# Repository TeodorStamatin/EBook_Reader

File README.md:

# EBook_Reader

## Block Diagram

## BOM (Bill Of Materials)

| Component  | Supplier Link | Datasheet |
|------------|---------------|-----------|
| 112A-TAAR-R03 | [Model](https://www.snapeda.com/parts/112A-TAAR-R03/Attend/view-part/) | [Datasheet](https://www.snapeda.com/parts/112A-TAAR-R03/Attend/datasheet/) |
| 744043680 | [Model](https://ro.mouser.com/ProductDetail/Wurth-Elektronik/744043680?qs=PGXP4M47uW6VkZq%252BkzjrHA%3D%3D) | [Datasheet](https://www.we-online.com/components/products/datasheet/744043680.pdf) |
| BD5229G-TR | [Model](https://www.digikey.ee/en/models/658502) | [Datasheet](https://www.rohm.com/datasheet?p=BD5229G&dist=Digi-key&media=referral&source=digi-key.com&campaign=Digi-key) |
| Capacitor 0402 | [Model](https://componentsearchengine.com/part-view/CC0402MRX5R5BB106/YAGEO) | [Datasheet](https://componentsearchengine.com/Datasheets/2/CC0402MRX5R5BB106.pdf) |
| CPH3225A | [Model](https://www.snapeda.com/parts/CPH3225A/Seiko+Instruments/view-part/?ref=eda) | [Datasheet](https://www.snapeda.com/parts/CPH3225A/Seiko%20Instruments/datasheet/) |
| Custom Button | [Model](https://industry.panasonic.com/global/en/products/control/switch/light-touch/number/evqpuj02k) | [Datasheet](https://industry.panasonic.com/global/en/downloads?tab=catalog&small_g_cd=203&part_no=EVQPUJ02K) |
| DS3231SN | [Model](https://www.snapeda.com/parts/DS3231SN%23/Analog+Devices/view-part/?ref=eda) | [Datasheet](https://www.snapeda.com/parts/DS3231SN%23/Analog%20Devices/datasheet/) |
| ESP32 WROVER 0805 Capacitor | [Model](https://ro.mouser.com/ProductDetail/KYOCERA-AVX/SD0805S020S1R0?qs=jCA%252BPfw4LHbpkAoSnwrdjw%3D%3D) | [Datasheet](https://ro.mouser.com/datasheet/2/40/schottky-3165252.pdf) |
| ESP32 WROVER BME680 Sensor | [Model](https://www.digikey.ro/en/models/7401317) | [Datasheet](https://www.bosch-sensortec.com/media/boschsensortec/downloads/datasheets/bst-bme680-ds001.pdf) |
| ESP32 WROVER MCP73831 Power Management | [Model](https://www.snapeda.com/parts/MCP73831T-2ACI/OT/Microchip/view-part/) | [Datasheet](https://www.snapeda.com/parts/MCP73831T-2ACI/OT/Microchip/datasheet/) |
| ESP32C6 Varistor 1812 | [Model](https://www.snapeda.com/parts/RC0603JR-070RL/Yageo/view-part/) | [Datasheet](https://www.snapeda.com/parts/RC0603JR-070RL/Yageo/datasheet/) |
| ESP32C6 WROOM-1-N8 | [Model](https://www.snapeda.com/parts/ESP32-C6-WROOM-1-N8/Espressif+Systems/view-part/?ref=eda) | [Datasheet](https://www.snapeda.com/parts/ESP32-C6-WROOM-1-N8/Espressif%20Systems/datasheet/) |
| FH34SRJ-24S-0.5SH | [Model](https://www.snapeda.com/parts/FH34SRJ-24S-0.5SH(99)/Hirose/view-part/) | [Datasheet](https://www.snapeda.com/parts/FH34SRJ-24S-0.5SH(99)/Hirose%20Connector/datasheet/) |
| LED Chip 0603 | [Model](https://grabcad.com/library/0603-smd-led-1) | [Datasheet](https://www.snapeda.com/parts/KP-1608SURCK/Kingbright/datasheet/) |
| MAX17048G+T10 | [Model](https://www.snapeda.com/parts/MAX17048G+T10/Analog+Devices/view-part/?ref=eda) | [Datasheet](https://www.snapeda.com/parts/MAX17048G+T10/Analog%20Devices/datasheet/) |
| MBR0530 Schottky Diode | [Model](https://www.snapeda.com/parts/MBR0530/Onsemi/view-part/?ref=eda) | [Datasheet](https://www.snapeda.com/parts/MBR0530/ON%20Semiconductor/datasheet/) |
| PGB1010603MR | [Model](https://www.snapeda.com/parts/PGB1010603MR/Littelfuse/view-part/?ref=eda) | [Datasheet](https://www.snapeda.com/parts/PGB1010603MR/Littelfuse%20Inc./datasheet/) |
| QWIIC Connector | [Model](https://www.snapeda.com/parts/PRT-14417/SparkFun/view-part/) | [Datasheet](https://www.snapeda.com/parts/PRT-14417/SparkFun%20Electronics/datasheet/) |
| RCL CPOL 3528 | [Model](https://www.snapeda.com/parts/TAJB475K025RNJ/AVX/view-part/?ref=dk&t=capacitor%203528&con_ref=None) | [Datasheet](https://s3.amazonaws.com/snapeda/datasheet/TAJB475K025RNJ_AVX.pdf) |
| Resistor 0402 | [Model](https://componentsearchengine.com/part-view/R0402%201%25%20100%20K%20(RC0402FR-07100KL)/YAGEO) | [Datasheet](https://www.yageo.com/upload/media/product/products/datasheet/rchip/PYu-RC_Group_51_RoHS_L_12.pdf) |
| SI1308EDL-T1-GE3 MOSFET | [Model](https://www.snapeda.com/parts/SI1308EDL-T1-GE3/Vishay+Siliconix/view-part/?ref=eda) | [Datasheet](https://www.snapeda.com/parts/SI1308EDL-T1-GE3/Vishay%20Siliconix/datasheet/) |
| SJ | [Model](https://grabcad.com/library/solder-jumpers-1) | [Datasheet]() |
| TPTP20R | [Model](https://ro.mouser.com/ProductDetail/Adafruit/3825?qs=%252bEew9%252b0nqrAn6n76%252bB5vZg%3D%3D&utm_source=findchips&utm_medium=aggregator&utm_campaign=3825&utm_term=3825&utm_content=Adafruit&_gl=1*1t6jdbp*_ga*MTQ5NTQ1ODI1LjE3NDMyMzgzNTY.*_ga_15W4STQT4T*MTc0Mzc4MDU5Ni4xMi4xLjE3NDM3ODM2MzIuNDIuMC4w) | [Datasheet](https://cdn-shop.adafruit.com/product-files/3825/3825_diagram.PDF) |
| USB4110-GF-A | [Model](https://componentsearchengine.com/part-view/USB4110-GF-A/GCT%20(GLOBAL%20CONNECTOR%20TECHNOLOGY)) | [Datasheet](https://gct.co/files/drawings/usb4110.pdf) |
| USBLC6-2SC6Y | [Model](https://www.snapeda.com/parts/USBLC6-2SC6Y/STMicroelectronics/view-part/?ref=eda) | [Datasheet](https://www.snapeda.com/parts/USBLC6-2SC6Y/STMicroelectronics/datasheet/) |
| W25Q512JVEIQ | [Model](https://www.digikey.ro/en/models/10244706) | [Datasheet](https://www.winbond.com/resource-files/W25Q512JV%20SPI%20RevB%2006252019%20KMS.pdf) |
| XC6220A331MR-G | [Model](https://componentsearchengine.com/part-view/XC6220A331MR-G/Torex) | [Datasheet](https://product.torexsemi.com/system/files/series/xc6220.pdf) |

## Hardware Description
1. Microcontroller - ESP32-C6-WROOM-1-N8
The ESP32-C6 is the core processing unit responsible for handling all system operations, communication with sensors and modules, and power management.
- Architecture: RISC-V 32-bit
- Clock Speed: 160 MHz
- Wireless Connectivity: 2.4 GHz Wi-Fi 6, Bluetooth 5.0

2. Power Management & Battery
Battery Type: Li-Po (Lithium Polymer)
- Capacity: 3.7V, 1800mAh
- Charging Circuit: MCP73831T
- Input Voltage: 5V via USB-C
- Protection Features: Overcharge and deep discharge protection
- Voltage Regulator: LDO regulator ensures a stable 3.3V power supply to all components.

3. Display - E-Paper (E-Ink) Screen
- Size: 7.5 inches
- Resolution: 800x480 pixels
- Communication Interface: SPI

4. SD Card Module
- Type: MicroSD (Supports FAT32)
- Interface: SPI

5. External NOR Flash
- Capacity: 64MB
- Interface: SPI

6. Environmental Sensor - BME688
- Functions: Measures temperature, humidity, air pressure, and gas levels.
- Communication Interface: I2C

7. Real-Time Clock (RTC) - DS3231SN
- Functionality: Maintains time and date even when the system is powered off.
- Communication Interface: I2C

8. USB-C Connector & ESD Protection
- Functionality: Provides power input and data transfer capability.
- Protection: Integrated ESD protection and Schottky diode for reverse polarity safety.

9. Buttons & User Input
- Tactile Push Buttons

10. Communication Interfaces
- GPIO: Used for button controls and general I/O operations.
- SPI: Used for SD card, external flash memory, and e-paper display.
- I2C: Used for the BME688 environmental sensor and DS3231SN RTC module.
- UART: Used for debugging and serial communication.
- Wi-Fi & Bluetooth: Provided by ESP32-C6, allowing wireless connectivity.

## Power Consumption Estimation
| Component                | Current Draw (mA) | Voltage (V) | Power (mW) |
|--------------------------|------------------|-------------|------------|
| **ESP32-C6 (Wi-Fi active)** | 200             | 3.3         | 660        |
| **E-Paper Display (Updating)** | 40        | 3.3         | 132        |
| **BME688 Sensor (Measuring)**  | 3.1       | 3.3         | 10.23      |
| **RTC Module (Active)**        | 0.15      | 3.3         | 0.495      |
| **SD Card (Active)**           | 50        | 3.3         | 165        |
| **External NOR Flash**         | 25        | 3.3         | 82.5       |
| **Total Estimated Power Consumption** | **~318.5mA** | 3.3V | **1050.72 mW** |

## ESP32-C6 Pin Mapping  

| Component                | ESP32-C6 Pin(s) | Interface | Purpose |
|--------------------------|----------------|-----------|---------|
| **E-Paper Display**      | IO7 (MOSI), IO6 (SCK), IO10 (CS), IO5 (DC), IO23 (RST), IO3 (BUSY) | SPI | Transfers image data to the display and controls its state. |
| **MicroSD Card**         | IO7 (MOSI), IO6 (SCK), IO4 (SS_SD), IO2 (MISO) | SPI | Allows storage and retrieval of e-book files. |
| **Environmental Sensor (BME688)** | IO21 (SDA), IO22 (SCL) | I2C | Reads temperature, humidity, pressure, and air quality data. |
| **RTC Module (DS3231)**  | IO21 (SDA), IO22 (SCL), IO18 (RST), IO1 (32KHz), IO0 (INT_RTC) | I2C | Keeps track of time even when ESP32 is off. |
| **External NOR Flash**   | IO11 (CS), IO6 (SCK), IO2 (MISO), IO7 (MOSI) | SPI | Provides additional storage for application data. |
| **Battery Monitoring**   | IO21 (SDA), IO22 (SCL) | I2C | Reads battery voltage and charge status. |
| **USB-C Connection**     | GPIOs through voltage regulation | USB | Powers and programs the ESP32-C6. |
| **Control Buttons**      | IO9 (BOOT), IO15 (CHANGE), EN (RESET) | GPIO | User input for device interactions. |

## Additional Design Notes  

- **Footprint Adjustments**:  
  - The **744043680 inductor** and **USB-C connector** footprints were modified to prevent design rule check (DRC) errors.  

- **Power Routing Constraints**:  
  - Not all power traces could be routed on the **top layer**, requiring some to be placed on the **bottom layer**.  
  - A **ground plane** is present on both the **top** and **bottom layers** for improved signal integrity and noise reduction.  

- **Component Placement**:  
  - The **component layout** closely follows the reference document to ensure optimal spacing and routing efficiency.  
  - The **battery fits perfectly** next to the PCB inside the enclosure.  

- **Button Alignment Issues**:  
  - The buttons **do not align perfectly** with their footprints, but they (hopefully) remain functional.  

- **Via Count and Stitching**:  
  - The design includes **79 vias**, which is a reasonable number for a project of this complexity.  
  - **Via stitching** was applied near the **ESP32-C6** to:  
    - Improve **ground return paths**.  
    - Manage **ground loops**.  
    - Enhance **heat dissipation**.  
    - Reduce **electromagnetic interference (EMI)**.

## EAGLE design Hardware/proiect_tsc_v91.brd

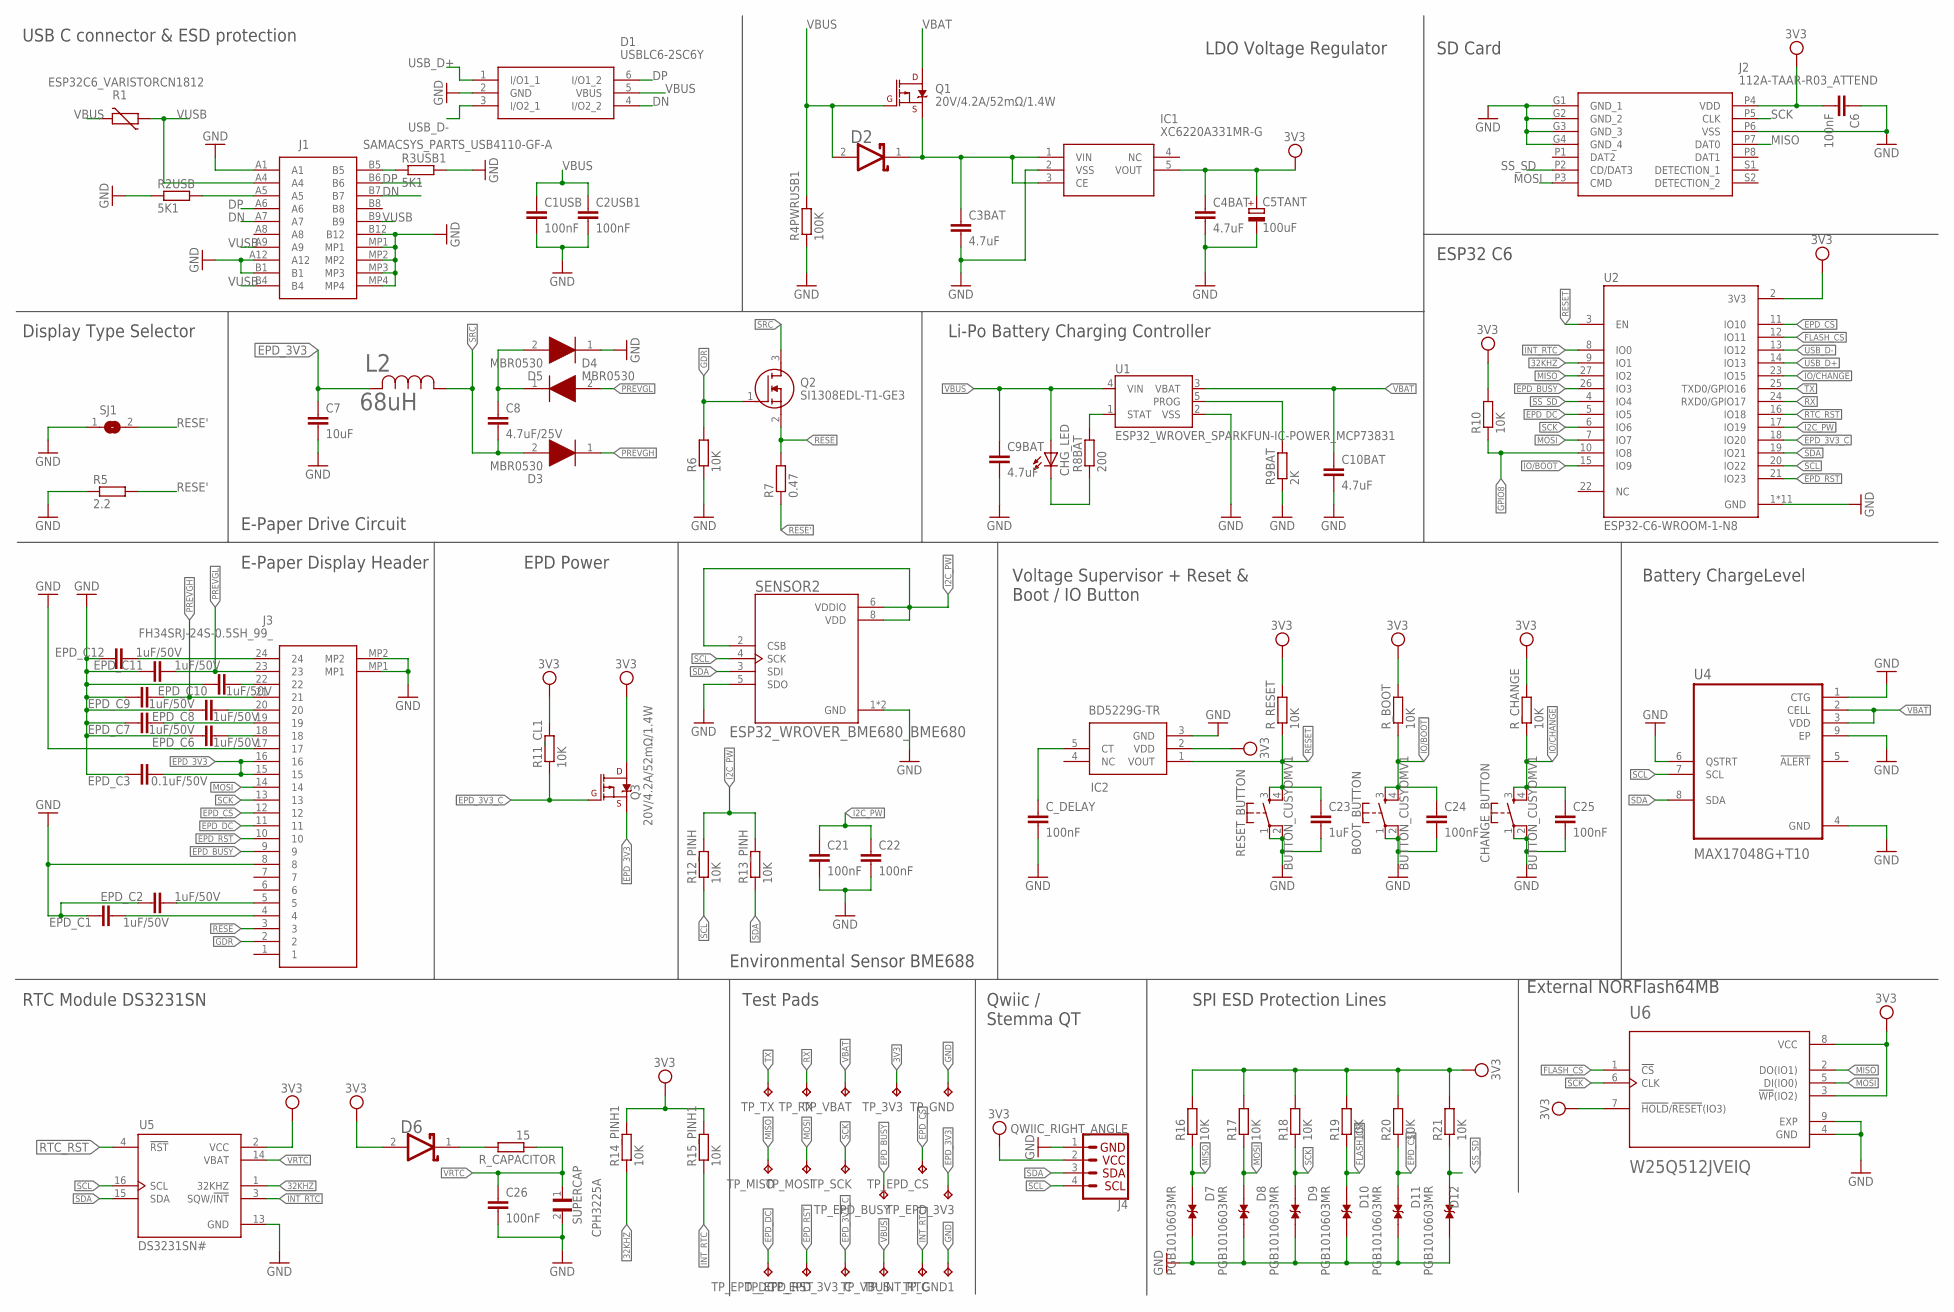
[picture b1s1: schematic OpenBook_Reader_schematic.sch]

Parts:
BOOT_BUTTON: BUTTON_CUSYOMV1; MYBUTTON
C1USB, C2USB1, C6, C21, C22, C24, C25, C26: 100nF; ESP32_WROVER_EAGLE-LTSPICE_C0402
C3BAT, C4BAT, C9BAT, C10BAT: 4.7uF; ESP32_WROVER_EAGLE-LTSPICE_C0402
C5TANT: 100uF; RCL_CT3528
C7: 10uF; ESP32_WROVER_EAGLE-LTSPICE_C0402
C8: 4.7uF/25V; ESP32_WROVER_EAGLE-LTSPICE_C0402
C23: 1uF; ESP32_WROVER_EAGLE-LTSPICE_C0402
CHANGE_BUTTON: BUTTON_CUSYOMV1; MYBUTTON
CHG_LED: ADAFRUIT_LEDCHIP-LED0603; ADAFRUIT_CHIP-LED0603
C_DELAY: 100nF; ESP32_WROVER_EAGLE-LTSPICE_C0402
D1: USBLC6-2SC6Y; SOT95P280X145-6N
D2, D6: ESP32_WROVER_AVX---SD0805S020S1R0_AVX_SD0805S020S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; ESP32_WROVER_AVX---SD0805S020S1R0_AVX_SD0805S020S1R0_0
D3, D4, D5: MBR0530; SOD3716X135N
D7, D8, D9, D10, D11, D12: PGB1010603MR; DIOC1608X36N
EPD_C1, EPD_C2, EPD_C6, EPD_C7, EPD_C8, EPD_C9, EPD_C10, EPD_C11, EPD_C12: 1uF/50V; ESP32_WROVER_EAGLE-LTSPICE_C0402
EPD_C3: 0.1uF/50V; ESP32_WROVER_EAGLE-LTSPICE_C0402
IC1: XC6220A331MR-G; SOT95P280X120-5N
IC2: BD5229G-TR; SOT95P280X125-5N
J1: SAMACSYS_PARTS_USB4110-GF-A; SAMACSYS_PARTS_USB4110GFA
J2: 112A-TAAR-R03_ATTEND; 112ATAARR03ATTEND
J3: FH34SRJ-24S-0.5SH_99_; FH34SRJ24S05SH99
J4: QWIIC_RIGHT_ANGLE; JST04_1MM_RA
L2: 68uH; IND_4828-WE-TPC_WRE
Q1, Q3: 20V/4.2A/52mΩ/1.4W; ESP32_WROVER_SPARKFUN-DISCRETESEMI_SOT23-3
Q2: SI1308EDL-T1-GE3; SOT65P210X110-3N
R1: ESP32C6_VARISTORCN1812; ESP32C6_VARISTOR_CT/CN1812
R2USB, R3USB1: 5K1; ESP32_WROVER_EAGLE-LTSPICE_R0402
R4PWRUSB1: 100K; ESP32_WROVER_EAGLE-LTSPICE_R0402
R5: 2.2; ESP32_WROVER_EAGLE-LTSPICE_R0402
R6, R10, R11_CL1, R12_PINH, R13_PINH, R14_PINH1, R15_PINH1, R16, R17, R18, R19, R20, R21: 10K; ESP32_WROVER_EAGLE-LTSPICE_R0402
R7: 0.47; ESP32_WROVER_EAGLE-LTSPICE_R0402
R8BAT: 200; ESP32_WROVER_EAGLE-LTSPICE_R0402
R9BAT: 2K; ESP32_WROVER_EAGLE-LTSPICE_R0402
RESET_BUTTON: BUTTON_CUSYOMV1; MYBUTTON
R_BOOT: 10K; ESP32_WROVER_EAGLE-LTSPICE_R0402
R_CAPACITOR: 15; ESP32_WROVER_EAGLE-LTSPICE_R0402
R_CHANGE: 10K; ESP32_WROVER_EAGLE-LTSPICE_R0402
R_RESET: 10K; ESP32_WROVER_EAGLE-LTSPICE_R0402
SENSOR2: ESP32_WROVER_BME680_BME680; ESP32_WROVER_BME680_PSON80P300X300X100-8N
SJ1: SJ
SUPERCAP: CPH3225A; CAPCP3225X100N
TP_3V3: TPTP20R; TP20R
TP_EPD_3V3, TP_EPD_3V3_C: TPTP20R; TP20R
TP_EPD_BUSY: TPTP20R; TP20R
TP_EPD_CS: TPTP20R; TP20R
TP_EPD_DC: TPTP20R; TP20R
TP_EPD_RST: TPTP20R; TP20R
TP_GND, TP_GND1: TPTP20R; TP20R
TP_INT_RTC: TPTP20R; TP20R
TP_MISO: TPTP20R; TP20R
TP_MOSI: TPTP20R; TP20R
TP_RX: TPTP20R; TP20R
TP_SCK: TPTP20R; TP20R
TP_TX: TPTP20R; TP20R
TP_VBAT: TPTP20R; TP20R
TP_VBUS: TPTP20R; TP20R
U1: ESP32_WROVER_SPARKFUN-IC-POWER_MCP73831; ESP32_WROVER_SPARKFUN-IC-POWER_SOT23-5
U2: ESP32-C6-WROOM-1-N8; XCVR_ESP32-C6-WROOM-1-N8
U4: MAX17048G+T10; SON50P200X200X80-9N
U5: DS3231SN#; SOIC127P1032X265-16N
U6: W25Q512JVEIQ; SON127P600X800X80-9N

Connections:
3V3: C4BAT.1, C5TANT.+, C6.2, D6.2 (ANODE), IC1.5 (VOUT), IC2.2 (VDD), J2.P4 (VDD), J4.2, Q3.3 (D), R10.2, R11_CL1.2, R14_PINH1.2, R15_PINH1.2, R16.2, R17.2, R18.2, R19.2, R20.2, R21.2, R_BOOT.2, R_CHANGE.2, R_RESET.2, TP_3V3.TP, U2.2 (3V3), U5.2 (VCC), U6.3 (!WP!(IO2)), U6.7 (!HOLD!/!RESET!(IO3)), U6.8 (VCC)
32KHZ: R14_PINH1.1, U2.9 (IO1), U5.1 (32KHZ)
DN: D1.4 (I/O2_2), J1.A7, J1.B7
DP: D1.6 (I/O1_2), J1.A6, J1.B6
EPD_3V3: C7.1, EPD_C3.2, J3.15, J3.16, L2.2, Q3.2 (S), TP_EPD_3V3.TP
EPD_3V3_C: Q3.1 (G), R11_CL1.1, TP_EPD_3V3_C.TP, U2.18 (IO20)
EPD_BUSY: J3.9, TP_EPD_BUSY.TP, U2.26 (IO3)
EPD_CS: D11.1, J3.12, R20.1, TP_EPD_CS.TP, U2.11 (IO10)
EPD_DC: J3.11, TP_EPD_DC.TP, U2.5 (IO5)
EPD_RST: J3.10, TP_EPD_RST.TP, U2.21 (IO23)
FLASH_CS: D10.1, R19.1, U2.12 (IO11), U6.1 (!CS)
GDR: J3.2, Q2.1 (G), R6.2
GND: BOOT_BUTTON.1, BOOT_BUTTON.2, C1USB.2, C2USB1.2, C3BAT.2, C4BAT.2, C5TANT.-, C6.1, C7.2, C9BAT.2, C10BAT.2, C21.2, C22.2, C23.2, C24.2, C25.2, C26.2, CHANGE_BUTTON.1, CHANGE_BUTTON.2, C_DELAY.2, D1.2 (GND), D5.1 (K), D7.2, D8.2, D9.2, D10.2, D11.2, D12.2, EPD_C1.1, EPD_C2.1, EPD_C3.1, EPD_C6.1, EPD_C7.1, EPD_C8.1, EPD_C9.1, EPD_C10.1, EPD_C11.1, EPD_C12.1, IC1.2 (VSS), IC2.3 (GND), J1.A1, J1.A12, J1.B1, J1.B12, J1.MP1, J1.MP2, J1.MP3, J1.MP4, J2.G1 (GND_1), J2.G2 (GND_2), J2.G3 (GND_3), J2.G4 (GND_4), J2.P6 (VSS), J3.8, J3.17, J3.MP1, J3.MP2, J4.1, R2USB.1, R3USB1.2, R4PWRUSB1.1, R5.1, R6.1, R9BAT.1, RESET_BUTTON.1, RESET_BUTTON.2, SENSOR2.1 (GND), SENSOR2.5 (SDO), SENSOR2.7 (GND), SJ1.1, SUPERCAP.2, TP_GND.TP, TP_GND1.TP, U1.2 (VSS), U2.1 (GND), U2.28 (GND), U2.29_1 (GND), U2.29_2 (GND), U2.29_3 (GND), U2.29_4 (GND), U2.29_5 (GND), U2.29_6 (GND), U2.29_7 (GND), U2.29_8 (GND), U2.29_9 (GND), U4.1 (CTG), U4.4 (GND), U4.6 (QSTRT), U4.9 (EP), U5.13 (GND), U6.4 (GND), U6.9 (EXP)
GPIO8: R10.1, U2.10 (IO8)
I2C_PW: C21.1, C22.1, R12_PINH.2, R13_PINH.2, SENSOR2.2 (CSB), SENSOR2.6 (VDDIO), SENSOR2.8 (VDD), U2.17 (IO19)
INT_RTC: R15_PINH1.1, TP_INT_RTC.TP, U2.8 (IO0), U5.3 (SQW/!INT)
IO/BOOT: BOOT_BUTTON.3, BOOT_BUTTON.4, C24.1, R_BOOT.1, U2.15 (IO9)
IO/CHANGE: C25.1, CHANGE_BUTTON.3, CHANGE_BUTTON.4, R_CHANGE.1, U2.23 (IO15)
MISO: D7.1, J2.P7 (DAT0), R16.1, TP_MISO.TP, U2.27 (IO2), U6.2 (DO(IO1))
MOSI: D8.1, J2.P3 (CMD), J3.14, R17.1, TP_MOSI.TP, U2.7 (IO7), U6.5 (DI(IO0))
unnamed: J1.A5, R2USB.2
unnamed: EPD_C6.2, J3.18
unnamed: EPD_C1.2, J3.4
unnamed: C3BAT.1, D2.1 (CATHODE), IC1.1 (VIN), IC1.3 (CE), Q1.2 (S)
unnamed: C8.1, D4.1 (K), D5.2 (A)
unnamed: R8BAT.2, U1.1 (STAT)
unnamed: CHG_LED.C, R8BAT.1
unnamed: R9BAT.2, U1.5 (PROG)
unnamed: EPD_C2.2, J3.5
unnamed: J1.B5, R3USB1.1
unnamed: EPD_C7.2, J3.19
unnamed: EPD_C8.2, J3.20
unnamed: C_DELAY.1, IC2.5 (CT)
unnamed: EPD_C10.2, J3.22
unnamed: D6.1 (CATHODE), R_CAPACITOR.2
unnamed: EPD_C12.2, J3.24
PREVGH: D3.1 (K), EPD_C9.2, J3.21
PREVGL: D4.2 (A), EPD_C11.2, J3.23
RESE: J3.3, Q2.2 (S), R7.2
RESE': R5.2, R7.1, SJ1.2
RESET: C23.1, IC2.1 (VOUT), RESET_BUTTON.3, RESET_BUTTON.4, R_RESET.1, U2.3 (EN)
RTC_RST: U2.16 (IO18), U5.4 (!RST)
RX: TP_RX.TP, U2.24 (RXD0/GPIO17)
SCK: D9.1, J2.P5 (CLK), J3.13, R18.1, TP_SCK.TP, U2.6 (IO6), U6.6 (CLK)
SCL: J4.4, R12_PINH.1, SENSOR2.4 (SCK), U2.20 (IO22), U4.7 (SCL), U5.16 (SCL)
SDA: J4.3, R13_PINH.1, SENSOR2.3 (SDI), U2.19 (IO21), U4.8 (SDA), U5.15 (SDA)
SRC: C8.2, D3.2 (A), L2.1, Q2.3 (D)
SS_SD: D12.1, J2.P2 (CD/DAT3), R21.1, U2.4 (IO4)
TX: TP_TX.TP, U2.25 (TXD0/GPIO16)
USB_D+: D1.1 (I/O1_1), U2.14 (IO13)
USB_D-: D1.3 (I/O2_1), U2.13 (IO12)
VBAT: C10BAT.1, Q1.3 (D), TP_VBAT.TP, U1.3 (VBAT), U4.2 (CELL), U4.3 (VDD)
VBUS: C1USB.1, C2USB1.1, C9BAT.1, CHG_LED.A, D1.5 (VBUS), D2.2 (ANODE), Q1.1 (G), R1.2, R4PWRUSB1.2, TP_VBUS.TP, U1.4 (VIN)
VRTC: C26.1, R_CAPACITOR.1, SUPERCAP.1, U5.14 (VBAT)
VUSB: J1.A4, J1.A9, J1.B4, J1.B9, R1.1

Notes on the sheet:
USB C connector & ESD protection
LDO Voltage Regulator
SD Card
ESP32 C6
Li-Po Battery Charging Controller
E-Paper Drive Circuit
Display Type Selector
E-Paper Display Header
EPD Power
Environmental Sensor BME688
Voltage Supervisor + Reset & Boot / IO Button
Battery ChargeLevel
External NORFlash64MB
SPI ESD Protection Lines
Qwiic / Stemma QT
Test Pads
RTC Module DS3231SN

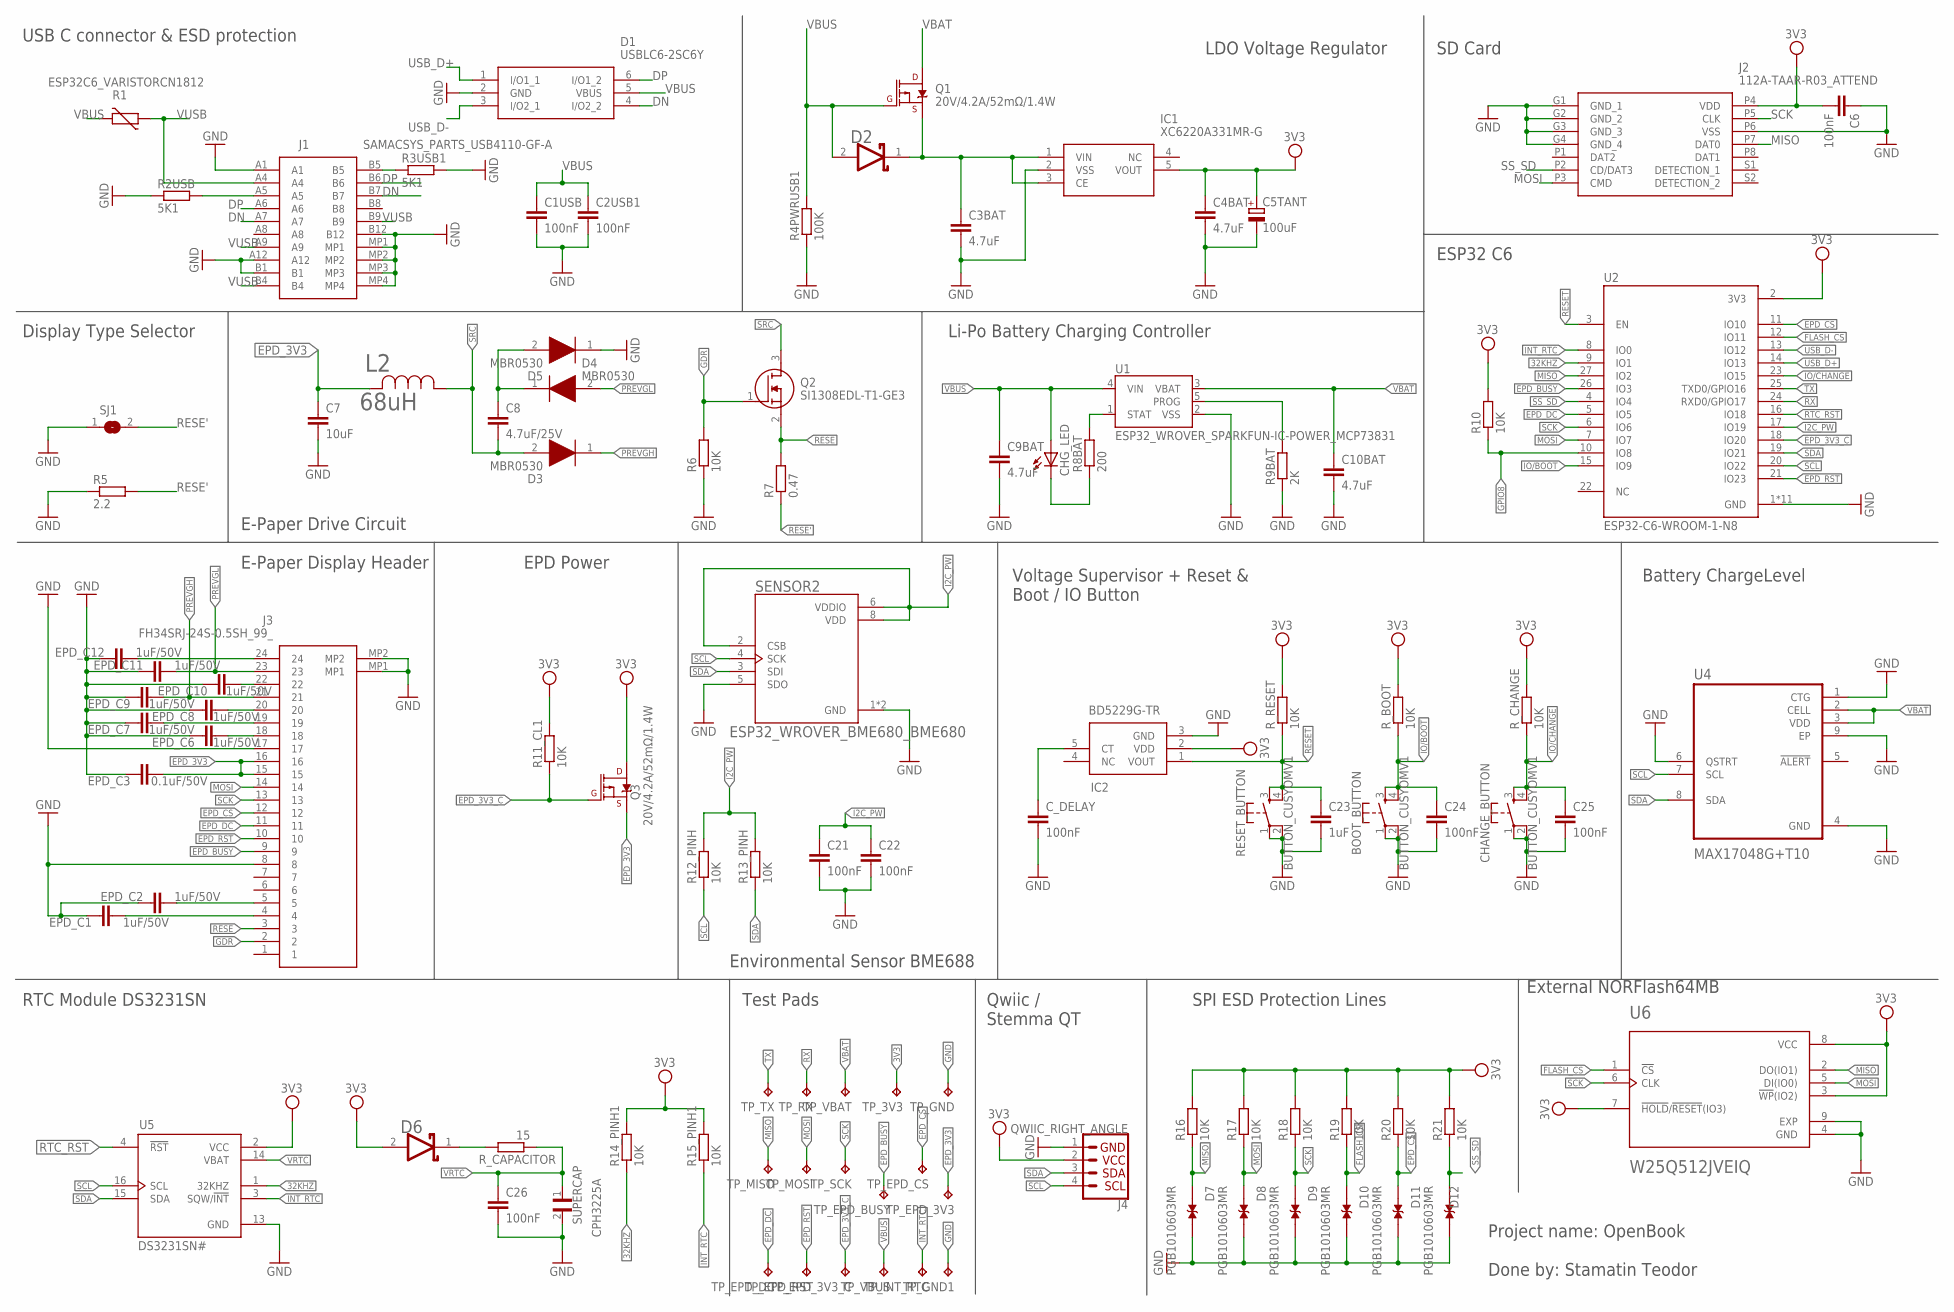
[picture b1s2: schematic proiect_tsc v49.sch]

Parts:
BOOT_BUTTON: BUTTON_CUSYOMV1; MYBUTTON
C1USB, C2USB1, C6, C21, C22, C24, C25, C26: 100nF; ESP32_WROVER_EAGLE-LTSPICE_C0402
C3BAT, C4BAT, C9BAT, C10BAT: 4.7uF; ESP32_WROVER_EAGLE-LTSPICE_C0402
C5TANT: 100uF; RCL_CT3528
C7: 10uF; ESP32_WROVER_EAGLE-LTSPICE_C0402
C8: 4.7uF/25V; ESP32_WROVER_EAGLE-LTSPICE_C0402
C23: 1uF; ESP32_WROVER_EAGLE-LTSPICE_C0402
CHANGE_BUTTON: BUTTON_CUSYOMV1; MYBUTTON
CHG_LED: ADAFRUIT_LEDCHIP-LED0603; ADAFRUIT_CHIP-LED0603
C_DELAY: 100nF; ESP32_WROVER_EAGLE-LTSPICE_C0402
D1: USBLC6-2SC6Y; SOT95P280X145-6N
D2, D6: ESP32_WROVER_AVX---SD0805S020S1R0_AVX_SD0805S020S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; ESP32_WROVER_AVX---SD0805S020S1R0_AVX_SD0805S020S1R0_0
D3, D4, D5: MBR0530; SOD3716X135N
D7, D8, D9, D10, D11, D12: PGB1010603MR; DIOC1608X36N
EPD_C1, EPD_C2, EPD_C6, EPD_C7, EPD_C8, EPD_C9, EPD_C10, EPD_C11, EPD_C12: 1uF/50V; ESP32_WROVER_EAGLE-LTSPICE_C0402
EPD_C3: 0.1uF/50V; ESP32_WROVER_EAGLE-LTSPICE_C0402
IC1: XC6220A331MR-G; SOT95P280X120-5N
IC2: BD5229G-TR; SOT95P280X125-5N
J1: SAMACSYS_PARTS_USB4110-GF-A; SAMACSYS_PARTS_USB4110GFA
J2: 112A-TAAR-R03_ATTEND; 112ATAARR03ATTEND
J3: FH34SRJ-24S-0.5SH_99_; FH34SRJ24S05SH99
J4: QWIIC_RIGHT_ANGLE; JST04_1MM_RA
L2: 68uH; IND_4828-WE-TPC_WRE
Q1, Q3: 20V/4.2A/52mΩ/1.4W; ESP32_WROVER_SPARKFUN-DISCRETESEMI_SOT23-3
Q2: SI1308EDL-T1-GE3; SOT65P210X110-3N
R1: ESP32C6_VARISTORCN1812; ESP32C6_VARISTOR_CT/CN1812
R2USB, R3USB1: 5K1; ESP32_WROVER_EAGLE-LTSPICE_R0402
R4PWRUSB1: 100K; ESP32_WROVER_EAGLE-LTSPICE_R0402
R5: 2.2; ESP32_WROVER_EAGLE-LTSPICE_R0402
R6, R10, R11_CL1, R12_PINH, R13_PINH, R14_PINH1, R15_PINH1, R16, R17, R18, R19, R20, R21: 10K; ESP32_WROVER_EAGLE-LTSPICE_R0402
R7: 0.47; ESP32_WROVER_EAGLE-LTSPICE_R0402
R8BAT: 200; ESP32_WROVER_EAGLE-LTSPICE_R0402
R9BAT: 2K; ESP32_WROVER_EAGLE-LTSPICE_R0402
RESET_BUTTON: BUTTON_CUSYOMV1; MYBUTTON
R_BOOT: 10K; ESP32_WROVER_EAGLE-LTSPICE_R0402
R_CAPACITOR: 15; ESP32_WROVER_EAGLE-LTSPICE_R0402
R_CHANGE: 10K; ESP32_WROVER_EAGLE-LTSPICE_R0402
R_RESET: 10K; ESP32_WROVER_EAGLE-LTSPICE_R0402
SENSOR2: ESP32_WROVER_BME680_BME680; ESP32_WROVER_BME680_PSON80P300X300X100-8N
SJ1: SJ
SUPERCAP: CPH3225A; CAPCP3225X100N
TP_3V3: TPTP20R; TP20R
TP_EPD_3V3, TP_EPD_3V3_C: TPTP20R; TP20R
TP_EPD_BUSY: TPTP20R; TP20R
TP_EPD_CS: TPTP20R; TP20R
TP_EPD_DC: TPTP20R; TP20R
TP_EPD_RST: TPTP20R; TP20R
TP_GND, TP_GND1: TPTP20R; TP20R
TP_INT_RTC: TPTP20R; TP20R
TP_MISO: TPTP20R; TP20R
TP_MOSI: TPTP20R; TP20R
TP_RX: TPTP20R; TP20R
TP_SCK: TPTP20R; TP20R
TP_TX: TPTP20R; TP20R
TP_VBAT: TPTP20R; TP20R
TP_VBUS: TPTP20R; TP20R
U1: ESP32_WROVER_SPARKFUN-IC-POWER_MCP73831; ESP32_WROVER_SPARKFUN-IC-POWER_SOT23-5
U2: ESP32-C6-WROOM-1-N8; XCVR_ESP32-C6-WROOM-1-N8
U4: MAX17048G+T10; SON50P200X200X80-9N
U5: DS3231SN#; SOIC127P1032X265-16N
U6: W25Q512JVEIQ; SON127P600X800X80-9N

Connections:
3V3: C4BAT.1, C5TANT.+, C6.2, D6.2 (ANODE), IC1.5 (VOUT), IC2.2 (VDD), J2.P4 (VDD), J4.2, Q3.3 (D), R10.2, R11_CL1.2, R14_PINH1.2, R15_PINH1.2, R16.2, R17.2, R18.2, R19.2, R20.2, R21.2, R_BOOT.2, R_CHANGE.2, R_RESET.2, TP_3V3.TP, U2.2 (3V3), U5.2 (VCC), U6.3 (!WP!(IO2)), U6.7 (!HOLD!/!RESET!(IO3)), U6.8 (VCC)
32KHZ: R14_PINH1.1, U2.9 (IO1), U5.1 (32KHZ)
DN: D1.4 (I/O2_2), J1.A7, J1.B7
DP: D1.6 (I/O1_2), J1.A6, J1.B6
EPD_3V3: C7.1, EPD_C3.2, J3.15, J3.16, L2.2, Q3.2 (S), TP_EPD_3V3.TP
EPD_3V3_C: Q3.1 (G), R11_CL1.1, TP_EPD_3V3_C.TP, U2.18 (IO20)
EPD_BUSY: J3.9, TP_EPD_BUSY.TP, U2.26 (IO3)
EPD_CS: D11.1, J3.12, R20.1, TP_EPD_CS.TP, U2.11 (IO10)
EPD_DC: J3.11, TP_EPD_DC.TP, U2.5 (IO5)
EPD_RST: J3.10, TP_EPD_RST.TP, U2.21 (IO23)
FLASH_CS: D10.1, R19.1, U2.12 (IO11), U6.1 (!CS)
GDR: J3.2, Q2.1 (G), R6.2
GND: BOOT_BUTTON.1, BOOT_BUTTON.2, C1USB.2, C2USB1.2, C3BAT.2, C4BAT.2, C5TANT.-, C6.1, C7.2, C9BAT.2, C10BAT.2, C21.2, C22.2, C23.2, C24.2, C25.2, C26.2, CHANGE_BUTTON.1, CHANGE_BUTTON.2, C_DELAY.2, D1.2 (GND), D5.1 (K), D7.2, D8.2, D9.2, D10.2, D11.2, D12.2, EPD_C1.1, EPD_C2.1, EPD_C3.1, EPD_C6.1, EPD_C7.1, EPD_C8.1, EPD_C9.1, EPD_C10.1, EPD_C11.1, EPD_C12.1, IC1.2 (VSS), IC2.3 (GND), J1.A1, J1.A12, J1.B1, J1.B12, J1.MP1, J1.MP2, J1.MP3, J1.MP4, J2.G1 (GND_1), J2.G2 (GND_2), J2.G3 (GND_3), J2.G4 (GND_4), J2.P6 (VSS), J3.8, J3.17, J3.MP1, J3.MP2, J4.1, R2USB.1, R3USB1.2, R4PWRUSB1.1, R5.1, R6.1, R9BAT.1, RESET_BUTTON.1, RESET_BUTTON.2, SENSOR2.1 (GND), SENSOR2.5 (SDO), SENSOR2.7 (GND), SJ1.1, SUPERCAP.2, TP_GND.TP, TP_GND1.TP, U1.2 (VSS), U2.1 (GND), U2.28 (GND), U2.29_1 (GND), U2.29_2 (GND), U2.29_3 (GND), U2.29_4 (GND), U2.29_5 (GND), U2.29_6 (GND), U2.29_7 (GND), U2.29_8 (GND), U2.29_9 (GND), U4.1 (CTG), U4.4 (GND), U4.6 (QSTRT), U4.9 (EP), U5.13 (GND), U6.4 (GND), U6.9 (EXP)
GPIO8: R10.1, U2.10 (IO8)
I2C_PW: C21.1, C22.1, R12_PINH.2, R13_PINH.2, SENSOR2.2 (CSB), SENSOR2.6 (VDDIO), SENSOR2.8 (VDD), U2.17 (IO19)
INT_RTC: R15_PINH1.1, TP_INT_RTC.TP, U2.8 (IO0), U5.3 (SQW/!INT)
IO/BOOT: BOOT_BUTTON.3, BOOT_BUTTON.4, C24.1, R_BOOT.1, U2.15 (IO9)
IO/CHANGE: C25.1, CHANGE_BUTTON.3, CHANGE_BUTTON.4, R_CHANGE.1, U2.23 (IO15)
MISO: D7.1, J2.P7 (DAT0), R16.1, TP_MISO.TP, U2.27 (IO2), U6.2 (DO(IO1))
MOSI: D8.1, J2.P3 (CMD), J3.14, R17.1, TP_MOSI.TP, U2.7 (IO7), U6.5 (DI(IO0))
unnamed: J1.A5, R2USB.2
unnamed: EPD_C6.2, J3.18
unnamed: EPD_C1.2, J3.4
unnamed: C3BAT.1, D2.1 (CATHODE), IC1.1 (VIN), IC1.3 (CE), Q1.2 (S)
unnamed: C8.1, D4.1 (K), D5.2 (A)
unnamed: R8BAT.2, U1.1 (STAT)
unnamed: CHG_LED.C, R8BAT.1
unnamed: R9BAT.2, U1.5 (PROG)
unnamed: EPD_C2.2, J3.5
unnamed: J1.B5, R3USB1.1
unnamed: EPD_C7.2, J3.19
unnamed: EPD_C8.2, J3.20
unnamed: C_DELAY.1, IC2.5 (CT)
unnamed: EPD_C10.2, J3.22
unnamed: D6.1 (CATHODE), R_CAPACITOR.2
unnamed: EPD_C12.2, J3.24
PREVGH: D3.1 (K), EPD_C9.2, J3.21
PREVGL: D4.2 (A), EPD_C11.2, J3.23
RESE: J3.3, Q2.2 (S), R7.2
RESE': R5.2, R7.1, SJ1.2
RESET: C23.1, IC2.1 (VOUT), RESET_BUTTON.3, RESET_BUTTON.4, R_RESET.1, U2.3 (EN)
RTC_RST: U2.16 (IO18), U5.4 (!RST)
RX: TP_RX.TP, U2.24 (RXD0/GPIO17)
SCK: D9.1, J2.P5 (CLK), J3.13, R18.1, TP_SCK.TP, U2.6 (IO6), U6.6 (CLK)
SCL: J4.4, R12_PINH.1, SENSOR2.4 (SCK), U2.20 (IO22), U4.7 (SCL), U5.16 (SCL)
SDA: J4.3, R13_PINH.1, SENSOR2.3 (SDI), U2.19 (IO21), U4.8 (SDA), U5.15 (SDA)
SRC: C8.2, D3.2 (A), L2.1, Q2.3 (D)
SS_SD: D12.1, J2.P2 (CD/DAT3), R21.1, U2.4 (IO4)
TX: TP_TX.TP, U2.25 (TXD0/GPIO16)
USB_D+: D1.1 (I/O1_1), U2.14 (IO13)
USB_D-: D1.3 (I/O2_1), U2.13 (IO12)
VBAT: C10BAT.1, Q1.3 (D), TP_VBAT.TP, U1.3 (VBAT), U4.2 (CELL), U4.3 (VDD)
VBUS: C1USB.1, C2USB1.1, C9BAT.1, CHG_LED.A, D1.5 (VBUS), D2.2 (ANODE), Q1.1 (G), R1.2, R4PWRUSB1.2, TP_VBUS.TP, U1.4 (VIN)
VRTC: C26.1, R_CAPACITOR.1, SUPERCAP.1, U5.14 (VBAT)
VUSB: J1.A4, J1.A9, J1.B4, J1.B9, R1.1

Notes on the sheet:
USB C connector & ESD protection
LDO Voltage Regulator
SD Card
ESP32 C6
Li-Po Battery Charging Controller
E-Paper Drive Circuit
Display Type Selector
E-Paper Display Header
EPD Power
Environmental Sensor BME688
Voltage Supervisor + Reset & Boot / IO Button
Battery ChargeLevel
External NORFlash64MB
SPI ESD Protection Lines
Qwiic / Stemma QT
Test Pads
RTC Module DS3231SN
Project name: OpenBook Done by: Stamatin Teodor

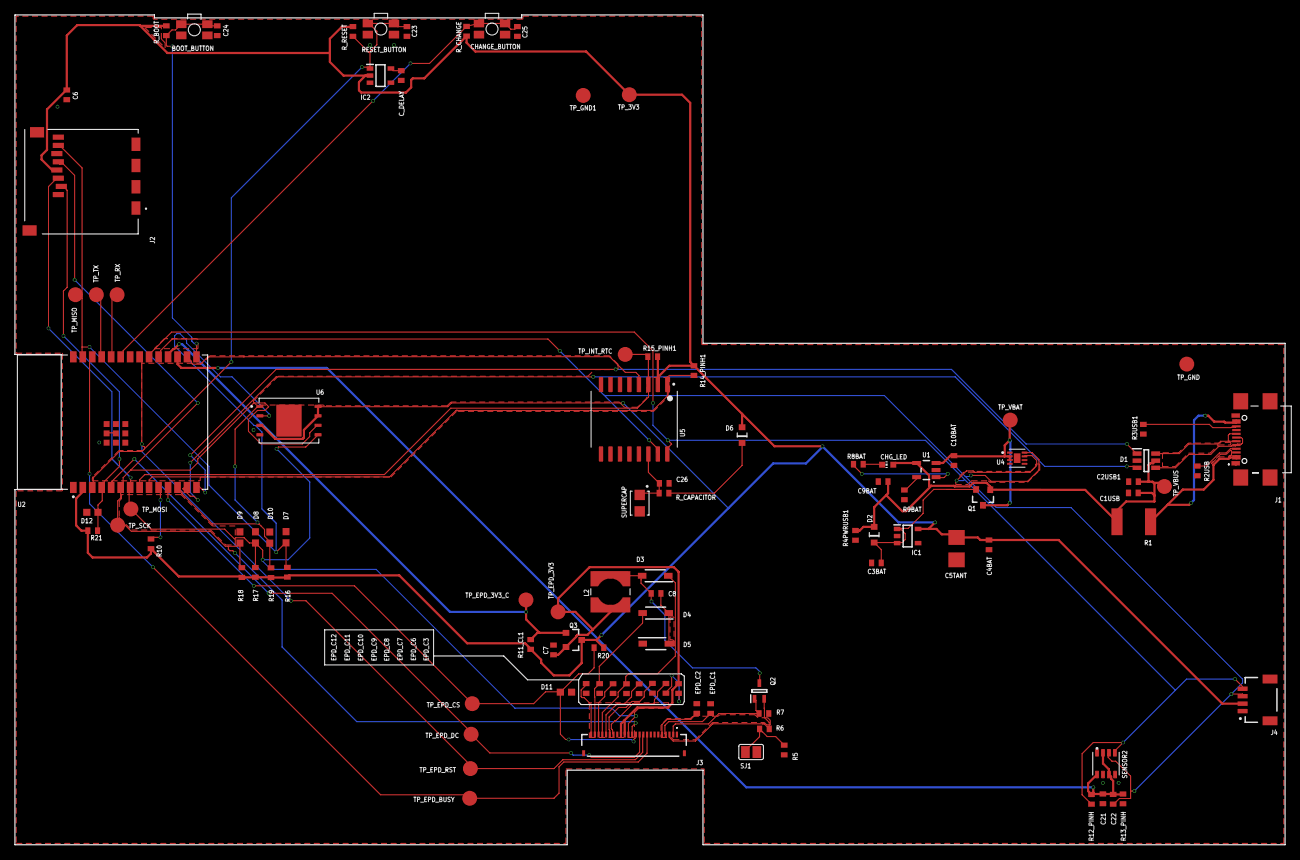
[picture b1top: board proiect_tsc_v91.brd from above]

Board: 2 copper layers, 170.2 x 111.2 mm, 103 parts (0 on the bottom side), 55 nets.

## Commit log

2025-04-01 step
2025-04-04 final maybe
2025-04-04 updated misspelling
2025-04-04 extension problem solved
2025-04-14 issuesDone

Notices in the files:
parts and their libraries:
DeskAssistant v19 v1: COPYRIGHT: Copyright (C) 2024 Ultra Librarian. All rights reserved.
